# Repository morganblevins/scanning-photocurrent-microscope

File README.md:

# scanning-photocurrent-microscope

| Todos | Description + Statues |
| --- | --- |
| `Integrate visible laser into SPCM; get first reflection image` | **Done:** Results below |
| `Get visible light photocurrent scan from PbTaSe2` | **In progress** |
| `Integrate QCL into SPCM` | **Not started** Need to order periscope equiptment |

This repository contains the following for the scanning photocurrent microscope in MIT META lab:
* MATLAB code for controlling and collecting measurments
* Comprehensive part list and photo documentation of build
* Preliminary data

Example of a scanning reflection map of a 30 micron gold cross mark compared to a microscope image

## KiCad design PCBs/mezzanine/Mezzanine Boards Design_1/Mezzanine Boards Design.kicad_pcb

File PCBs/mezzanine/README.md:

Mezzanine PCB designed by Jacqueline Wang during Spring 2024 UROP using KiCAD

https://gitlab.com/kicad/libraries/kicad-footprint-generator

the silicondie.py file was ran inside the library-> KiCADModTree->examples folder
### Rendering

### Pad numbering

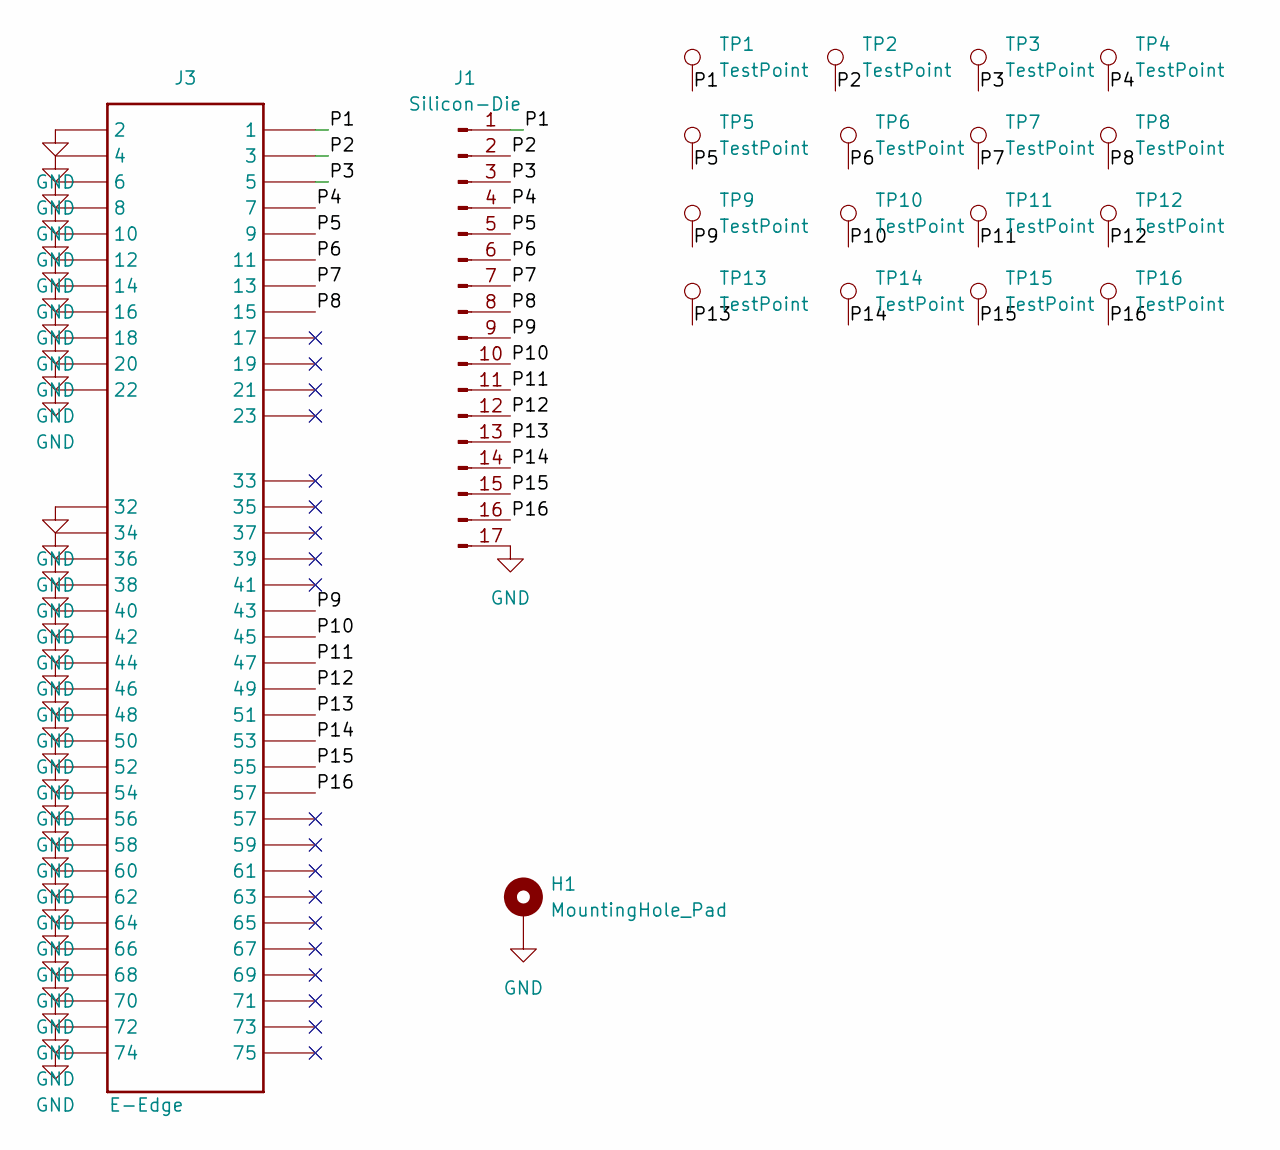
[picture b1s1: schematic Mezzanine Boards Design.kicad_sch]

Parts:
H1: MountingHole_Pad; MH_2mm
J1: Silicon-Die; new_sillicon_die_footprint
J3: E-Edge; E-Key_Edge
TP1, TP2, TP3, TP4, TP5, TP6, TP7, TP8, TP9, TP10, TP11, TP12, TP13, TP14, TP15, TP16: TestPoint; TestPoint_Pad_1.5x1.5mm

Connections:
/P1: J1.1, J3.1, TP1.1
/P2: J1.2, J3.3, TP2.1
/P3: J1.3, J3.5, TP3.1
/P4: J1.4, J3.7, TP4.1
/P5: J1.5, J3.9, TP5.1
/P6: J1.6, J3.11, TP6.1
/P7: J1.7, J3.13, TP7.1
/P8: J1.8, J3.15, TP8.1
/P9: J1.9, J3.43, TP9.1
/P10: J1.10, J3.45, TP10.1
/P11: J1.11, J3.47, TP11.1
/P12: J1.12, J3.49, TP12.1
/P13: J1.13, J3.51, TP13.1
/P14: J1.14, J3.53, TP14.1
/P15: J1.15, J3.55, TP15.1
/P16: J1.16, J3.57, TP16.1
GND: H1.1, J1.17, J3.2, J3.4, J3.6, J3.8, J3.10, J3.12, J3.14, J3.16, J3.18, J3.20, J3.22, J3.32, J3.34, J3.36, J3.38, J3.40, J3.42, J3.44, J3.46, J3.48, J3.50, J3.52, J3.54, J3.56, J3.58, J3.60, J3.62, J3.64, J3.66, J3.68, J3.70, J3.72, J3.74

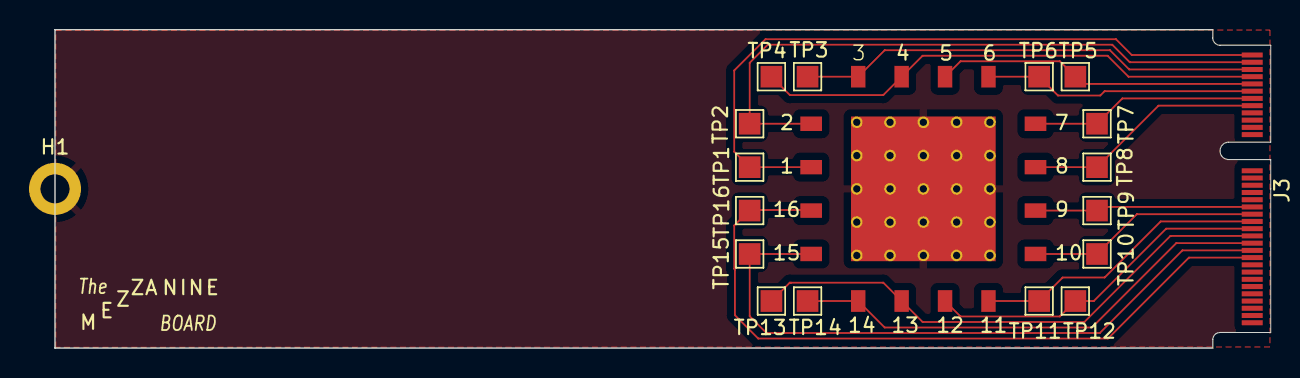
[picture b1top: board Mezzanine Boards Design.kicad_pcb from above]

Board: 2 copper layers, 84.0 x 22.0 mm, 19 parts (0 on the bottom side), 17 nets.

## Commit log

2024-03-01 Create initial-reflection-maps
2024-03-01 Rename initial-reflection-maps to initial-reflection-maps.md
2024-03-01 Rename initial reflection maps/cross_mark_00005.fig to initial reflection maps/data/cross_mark_00005.fig
2024-03-01 Rename initial reflection maps/cross_mark_00005_v2.fig to initial reflection maps/data/cross_mark_00005_v2.fig
2024-03-01 Rename initial reflection maps/cross_mark_0_00025mmsteps_02282024.fig to initial reflection maps/data/cross_mark_0_00025mmsteps_02282024.fig
2024-03-01 Rename initial reflection maps/cross_mark_0_00025mmsteps_02282024.mat to initial reflection maps/data/cross_mark_0_00025mmsteps_02282024.mat
2024-05-20 Rename PCBs/Gerber_PCB_UROP Project_2.zip to PCBs/mainboard/Gerber_PCB_UROP Project_2.zip
2024-06-11 Create MLS203_EMI
2024-06-11 Rename MLS203_EMI to MLS203_EMI.md
2024-06-11 Rename MLS203_EMI.md to Troubleshooting EMI/MLS203_EMI.md
2024-06-11 Add files via upload
    This is the code I used to control the MLS203 and the Keithley 6482 to make current measurements.
2024-06-11 Rename MLS203_EMI.md to README.md
2024-06-11 Add files via upload
    Documentation of Mezzanine board and electrode design code
2024-06-11 Rename PbTaSe2-experiment-May-20-2024.md to Experiment-May-20-2024.md
2024-06-11 Rename Experiment-May-20-2024.md to SPCM Experiments/Experiment-May-20-2024.md
2024-07-02 June-July: Post EMI troubleshooting- sample and alignment.md
2024-07-05 Rename Experiment-May-20-2024.md to EMI - SPCM - May 20 2024.md
2024-07-05 Rename June 28- Post EMI troubleshooting- next steps.md to Post EMI troubleshooting - next steps - SPCM - June 28 2024.md
